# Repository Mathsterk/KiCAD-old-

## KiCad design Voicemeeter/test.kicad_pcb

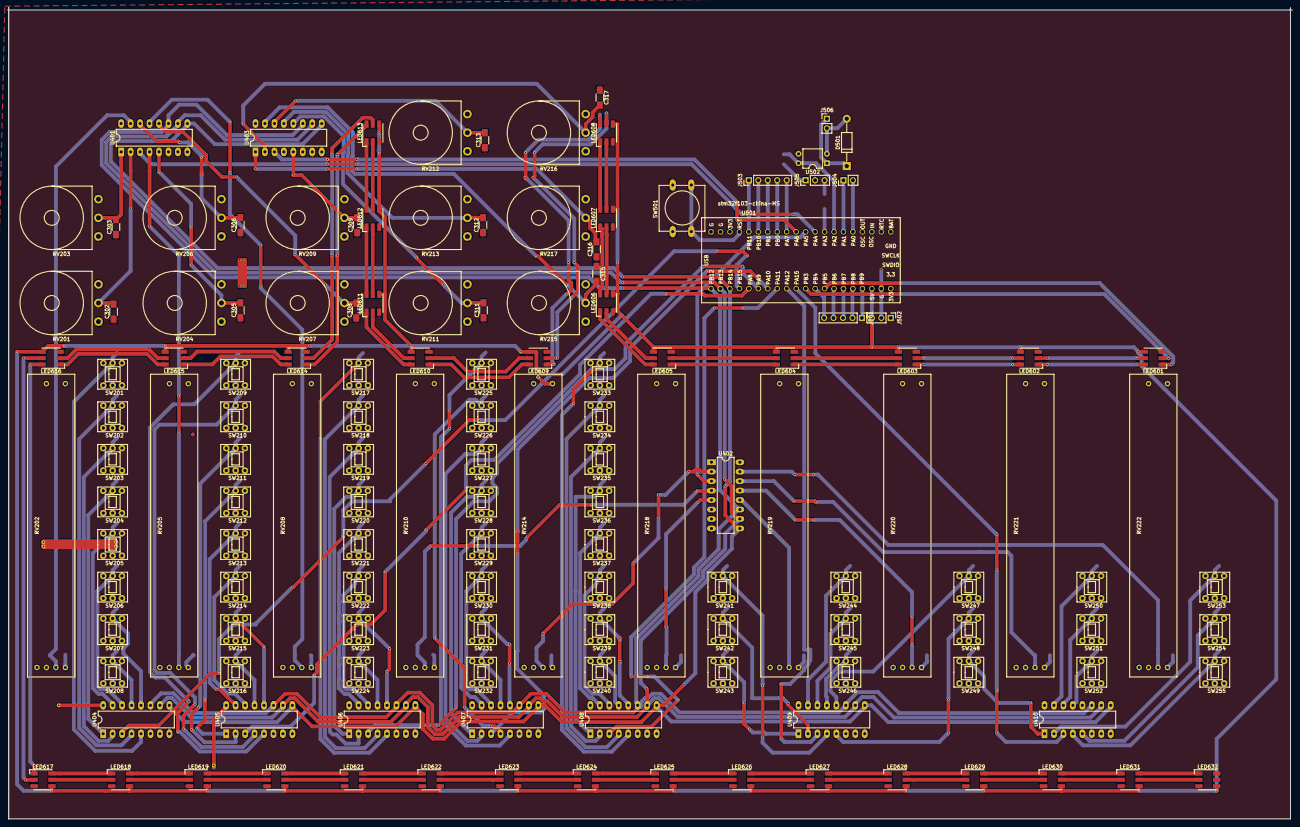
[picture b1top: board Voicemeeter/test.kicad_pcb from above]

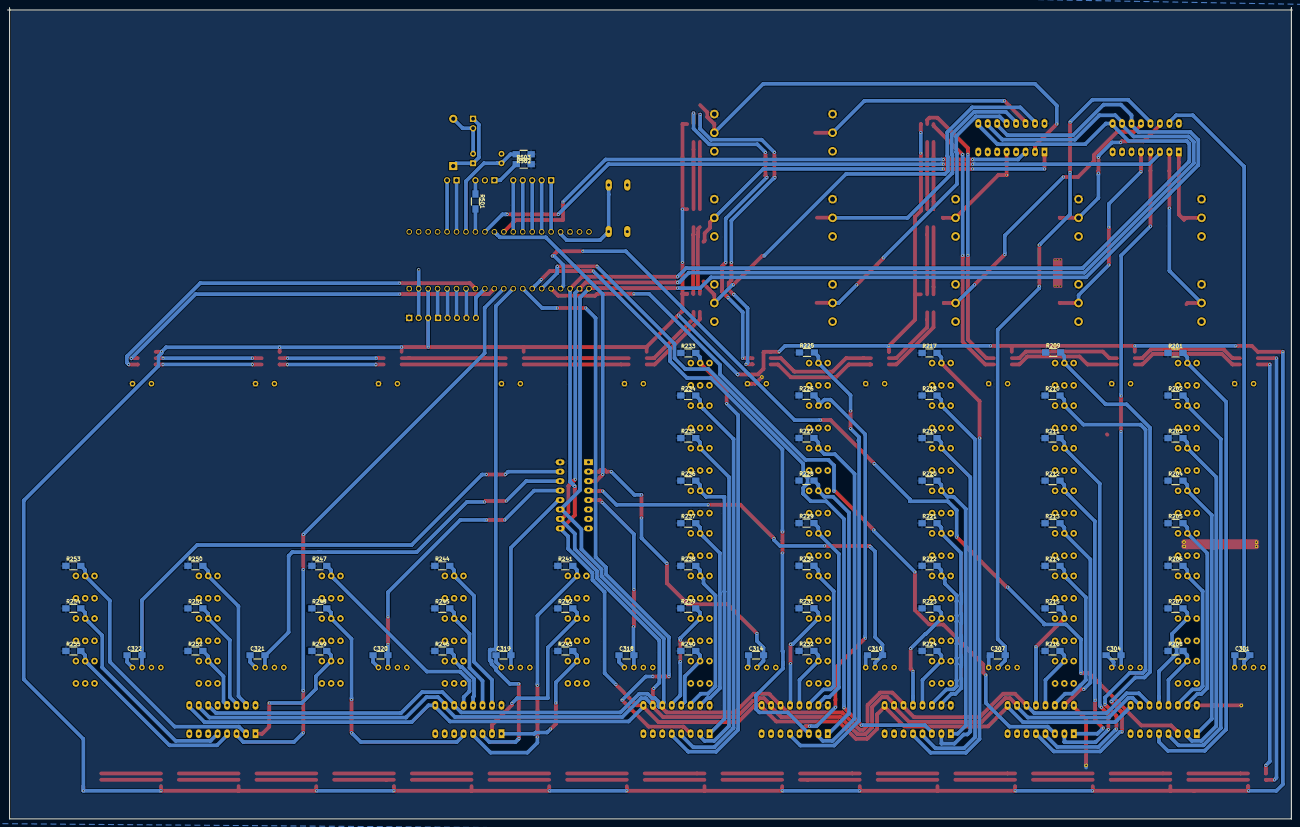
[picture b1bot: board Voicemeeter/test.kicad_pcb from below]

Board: 2 copper layers, 344.9 x 217.8 mm, 209 parts (68 on the bottom side), 176 nets.

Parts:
C301, C302, C303, C304, C305, C306, C307, C308, C309, C310, C311, C312, C313, C314, C315, C316, C317, C318, C319, C320, C321, C322: 10uF; C_1206_HandSoldering
D501: D; D_DO-41_SOD81_P12.70mm_Horizontal
J501, J503: CONN_01X05; Pin_Header_Straight_1x05_Pitch2.54mm
J502, J505: CONN_01X03; Pin_Header_Straight_1x03_Pitch2.54mm
J504, J506: CONN_01X02; Pin_Header_Straight_1x02_Pitch2.54mm
LED601, LED602, LED603, LED604, LED605, LED606, LED607, LED608, LED609, LED610, LED611, LED612, LED613, LED614, LED615, LED616, LED617, LED618, LED619, LED620, LED621, LED622, LED623, LED624, LED625, LED626, LED627, LED628, LED629, LED630, LED631, LED632: SK9822; LED_RGB_5050-6
R201, R202, R203, R204, R205, R206, R207, R208, R209, R210, R211, R212, R213, R214, R215, R216, R217, R218, R219, R220, R221, R222, R223, R224, R225, R226, R227, R228, R229, R230, R231, R232, R233, R234, R235, R236, R237, R238, R239, R240, R241, R242, R243, R244, R245, R246, R247, R248, R249, R250, R251, R252, R253, R254, R255: 10K; R_1206_HandSoldering
R501, R503: 220R; R_1206_HandSoldering
R502: 330R; R_1206_HandSoldering
RV201, RV203, RV204, RV206, RV207, RV209, RV211, RV212, RV213, RV215, RV216, RV217: POT; Potentiometer_Omeg_PC16PU_Horizontal
RV202, RV205, RV208, RV210, RV214, RV218, RV219, RV220, RV221, RV222: SLIDEPOT; slidepot
SW201, SW202, SW203, SW204, SW205, SW206, SW207, SW208, SW209, SW210, SW211, SW212, SW213, SW214, SW215, SW216, SW217, SW218, SW219, SW220, SW221, SW222, SW223, SW224, SW225, SW226, SW227, SW228, SW229, SW230, SW231, SW232, SW233, SW234, SW235, SW236, SW237, SW238, SW239, SW240, SW241, SW242, SW243, SW244, SW245, SW246, SW247, SW248, SW249, SW250, SW251, SW252, SW253, SW254, SW255: SW_SPDT_6pin; 8mm_push_button
SW501: SW_Push; SW_PUSH-12mm
U401, U402, U403, U404, U405, U406, U407, U408, U409, U410: 74HC4051; DIP-16_W7.62mm_LongPads
U501: stm32f103-china-MS; stm32f103c8t6-module-china-MS
U502: PC817; DIP-4_W7.62mm

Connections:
+3V3: J502.1, R201.1, R202.1, R203.1, R204.1, R205.1, R206.1, R207.1, R208.1, R209.1, R210.1, R211.1, R212.1, R213.1, R214.1, R215.1, R216.1, R217.1, R218.1, R219.1, R220.1, R221.1, R222.1, R223.1, R224.1, R225.1, R226.1, R227.1, R228.1, R229.1, R230.1, R231.1, R232.1, R233.1, R234.1, R235.1, R236.1, R237.1, R238.1, R239.1, R240.1, R241.1, R242.1, R243.1, R244.1, R245.1, R246.1, R247.1, R248.1, R249.1, R250.1, R251.1, R252.1, R253.1, R254.1, R255.1, R502.1, R503.2, RV201.1, RV202.3, RV203.1, RV204.1, RV205.3, RV206.1, RV207.1, RV208.3, RV209.1, RV210.3, RV211.1, RV212.1, RV213.1, RV214.3, RV215.1, RV216.1, RV217.1, RV218.3, RV219.3, RV220.3, RV221.3, RV222.3, U401.16, U402.16, U403.16, U404.16, U405.16, U406.16, U407.16, U408.16, U409.16, U410.16, U501.20, U501.38
+5V: J502.3, LED601.4, LED602.4, LED603.4, LED604.4, LED605.4, LED606.4, LED607.4, LED608.4, LED609.4, LED610.4, LED611.4, LED612.4, LED613.4, LED614.4, LED615.4, LED616.4, LED617.4, LED618.4, LED619.4, LED620.4, LED621.4, LED622.4, LED623.4, LED624.4, LED625.4, LED626.4, LED627.4, LED628.4, LED629.4, LED630.4, LED631.4, LED632.4, U501.18
/LED Driver/SK1: LED601.2, U501.11
/LED Driver/SK2: LED601.1, U501.13
/Mux/DA11: C310.2, RV210.2, U402.4
/Mux/DA12: C311.2, RV211.2, U403.12
/Mux/DA13: C312.2, RV213.2, U403.13
/Mux/DA14: C313.2, RV212.2, U403.14
/Mux/DA21: C314.2, RV214.2, U402.2
/Mux/DA22: C315.2, RV215.2, U403.15
/Mux/DA23: C316.2, RV217.2, U403.1
/Mux/DA24: C317.2, RV216.2, U403.2
/Mux/DD11: R225.2, SW225.1, U407.5
/Mux/DD12: R226.2, SW226.1, U407.4
/Mux/DD13: R227.2, SW227.1, U407.2
/Mux/DD14: R228.2, SW228.1, U407.1
/Mux/DD15: R229.2, SW229.1, U407.15
/Mux/DD16: R230.2, SW230.1, U407.14
/Mux/DD17: R231.2, SW231.1, U407.12
/Mux/DD18: R232.2, SW232.1, U407.13
/Mux/DD21: R233.2, SW233.1, U408.5
/Mux/DD22: R234.2, SW234.1, U408.4
/Mux/DD23: R235.2, SW235.1, U408.2
/Mux/DD24: R236.2, SW236.1, U408.1
/Mux/DD25: R237.2, SW237.1, U408.15
/Mux/DD26: R238.2, SW238.1, U408.14
/Mux/DD27: R239.2, SW239.1, U408.12
/Mux/DD28: R240.2, SW240.1, U408.13
/Mux/HA11: C301.2, RV202.2, U401.15
/Mux/HA12: C302.2, RV201.2, U401.2
/Mux/HA13: C303.2, RV203.2, U401.1
/Mux/HA21: C304.2, RV205.2, U401.4
/Mux/HA22: C305.2, RV204.2, U401.5
/Mux/HA23: C306.2, RV206.2, U401.14
/Mux/HA31: C307.2, RV208.2, U401.13
/Mux/HA32: C308.2, RV207.2, U401.12
/Mux/HA33: C309.2, RV209.2, U403.5
/Mux/HD11: R201.2, SW201.1, U404.5
/Mux/HD12: R202.2, SW202.1, U404.4
/Mux/HD13: R203.2, SW203.1, U404.2
/Mux/HD14: R204.2, SW204.1, U404.1
/Mux/HD15: R205.2, SW205.1, U404.15
/Mux/HD16: R206.2, SW206.1, U404.14
/Mux/HD17: R207.2, SW207.1, U404.12
/Mux/HD18: R208.2, SW208.1, U404.13
/Mux/HD21: R209.2, SW209.1, U405.5
/Mux/HD22: R210.2, SW210.1, U405.4
/Mux/HD23: R211.2, SW211.1, U405.2
/Mux/HD24: R212.2, SW212.1, U405.1
/Mux/HD25: R213.2, SW213.1, U405.15
/Mux/HD26: R214.2, SW214.1, U405.14
/Mux/HD27: R215.2, SW215.1, U405.12
/Mux/HD28: R216.2, SW216.1, U405.13
/Mux/HD31: R217.2, SW217.1, U406.5
/Mux/HD32: R218.2, SW218.1, U406.4
/Mux/HD33: R219.2, SW219.1, U406.2
/Mux/HD34: R220.2, SW220.1, U406.1
/Mux/HD35: R221.2, SW221.1, U406.15
/Mux/HD36: R222.2, SW222.1, U406.14
/Mux/HD37: R223.2, SW223.1, U406.12
/Mux/HD38: R224.2, SW224.1, U406.13
/Mux/M1: U401.11, U402.11, U403.11, U404.11, U405.11, U406.11, U407.11, U408.11, U409.11, U410.11, U501.1
/Mux/M2: U401.10, U402.10, U403.10, U404.10, U405.10, U406.10, U407.10, U408.10, U409.10, U410.10, U501.2
/Mux/M3: U401.9, U402.9, U403.9, U404.9, U405.9, U406.9, U407.9, U408.9, U409.9, U410.9, U501.3
/Mux/M11: U401.3, U501.29
/Mux/M12: U402.3, U501.30
/Mux/M13: U403.3, U501.31
/Mux/M21: U404.3, U501.4
/Mux/M22: U405.3, U501.5
/Mux/M23: U406.3, U501.6
/Mux/M24: U407.3, U501.7
/Mux/M25: U408.3, U501.8
/Mux/M26: U409.3, U501.9
/Mux/M27: U410.3, U501.10
/Mux/OA1: C318.2, RV218.2, U402.5
/Mux/OA2: C319.2, RV219.2, U402.12
/Mux/OA3: C320.2, RV220.2, U402.13
/Mux/OA4: C321.2, RV221.2, U402.14
/Mux/OA5: C322.2, RV222.2, U402.15
/Mux/OD11: R241.2, SW241.1, U409.4
/Mux/OD12: R242.2, SW242.1, U409.2
/Mux/OD13: R243.2, SW243.1, U409.1
/Mux/OD21: R244.2, SW244.1, U409.15
/Mux/OD22: R245.2, SW245.1, U409.14
/Mux/OD23: R246.2, SW246.1, U409.13
/Mux/OD31: R247.2, SW247.1, U409.12
/Mux/OD32: R248.2, SW248.1, U409.5
/Mux/OD33: R249.2, SW249.1, U410.1
/Mux/OD41: R250.2, SW250.1, U410.15
/Mux/OD42: R251.2, SW251.1, U410.14
/Mux/OD43: R252.2, SW252.1, U410.13
/Mux/OD51: R253.2, SW253.1, U410.2
/Mux/OD52: R254.2, SW254.1, U410.5
/Mux/OD53: R255.2, SW255.1, U410.4
GND: C301.1, C302.1, C303.1, C304.1, C305.1, C306.1, C307.1, C308.1, C309.1, C310.1, C311.1, C312.1, C313.1, C314.1, C315.1, C316.1, C317.1, C318.1, C319.1, C320.1, C321.1, C322.1, J502.2, J505.2, LED601.3, LED602.3, LED603.3, LED604.3, LED605.3, LED606.3, LED607.3, LED608.3, LED609.3, LED610.3, LED611.3, LED612.3, LED613.3, LED614.3, LED615.3, LED616.3, LED617.3, LED618.3, LED619.3, LED620.3, LED621.3, LED622.3, LED623.3, LED624.3, LED625.3, LED626.3, LED627.3, LED628.3, LED629.3, LED630.3, LED631.3, LED632.3, RV201.3, RV202.1, RV203.3, RV204.3, RV205.1, RV206.3, RV207.3, RV208.1, RV209.3, RV210.1, RV211.3, RV212.3, RV213.3, RV214.1, RV215.3, RV216.3, RV217.3, RV218.1, RV219.1, RV220.1, RV221.1, RV222.1, SW201.2, SW201.4, SW201.5, SW201.6, SW202.2, SW202.4, SW202.5, SW202.6, SW203.2, SW203.4, SW203.5, SW203.6, SW204.2, SW204.4, SW204.5, SW204.6, SW205.2, SW205.4, SW205.5, SW205.6, SW206.2, SW206.4, SW206.5, SW206.6, SW207.2, SW207.4, SW207.5, SW207.6, SW208.2, SW208.4, SW208.5, SW208.6, SW209.2, SW209.4, SW209.5, SW209.6, SW210.2, SW210.4, SW210.5, SW210.6, SW211.2, SW211.4, SW211.5, SW211.6, SW212.2, SW212.4, SW212.5, SW212.6, SW213.2, SW213.4, SW213.5, SW213.6, SW214.2, SW214.4, SW214.5, SW214.6, SW215.2, SW215.4, SW215.5, SW215.6, SW216.2, SW216.4, SW216.5, SW216.6, SW217.2, SW217.4, SW217.5, SW217.6, SW218.2, SW218.4, SW218.5, SW218.6, SW219.2, SW219.4, SW219.5, SW219.6, SW220.2, SW220.4, SW220.5, SW220.6, SW221.2, SW221.4, SW221.5, SW221.6, SW222.2, SW222.4, SW222.5, SW222.6, SW223.2, SW223.4, SW223.5, SW223.6, SW224.2, SW224.4, SW224.5, SW224.6, SW225.2, SW225.4, SW225.5, SW225.6, SW226.2, SW226.4, SW226.5, SW226.6, SW227.2, SW227.4, SW227.5, SW227.6, SW228.2, SW228.4, SW228.5, SW228.6, SW229.2, SW229.4, SW229.5, SW229.6, SW230.2, SW230.4, SW230.5, SW230.6, SW231.2, SW231.4, SW231.5, SW231.6, SW232.2, SW232.4, SW232.5, SW232.6, SW233.2, SW233.4, SW233.5, SW233.6, SW234.2, SW234.4, SW234.5, SW234.6, SW235.2, SW235.4, SW235.5, SW235.6, SW236.2, SW236.4, SW236.5, SW236.6, SW237.2, SW237.4, SW237.5, SW237.6, SW238.2, SW238.4, SW238.5, SW238.6, SW239.2, SW239.4, SW239.5, SW239.6, SW240.2, SW240.4, SW240.5, SW240.6, SW241.2, SW241.4, SW241.5, SW241.6, SW242.2, SW242.4, SW242.5, SW242.6, SW243.2, SW243.4, SW243.5, SW243.6, SW244.2, SW244.4, SW244.5, SW244.6, SW245.2, SW245.4, SW245.5, SW245.6, SW246.2, SW246.4, SW246.5, SW246.6, SW247.2, SW247.4, SW247.5, SW247.6, SW248.2, SW248.4, SW248.5, SW248.6, SW249.2, SW249.4, SW249.5, SW249.6, SW250.2, SW250.4, SW250.5, SW250.6, SW251.2, SW251.4, SW251.5, SW251.6, SW252.2, SW252.4, SW252.5, SW252.6, SW253.2, SW253.4, SW253.5, SW253.6, SW254.2, SW254.4, SW254.5, SW254.6, SW255.2, SW255.4, SW255.5, SW255.6, SW501.1, U401.8, U402.8, U403.8, U404.8, U405.8, U406.8, U407.8, U408.8, U409.8, U410.8, U501.19, U501.39, U501.40, U502.3
unnamed: D501.1, J506.1, U502.1
unnamed: D501.2, J506.2, U502.2
unnamed: J501.1, U501.17
unnamed: J501.2, U501.16
unnamed: J501.3, U501.15
unnamed: J501.4, U501.14
unnamed: J501.5, U501.12
unnamed: J503.1, U501.36
unnamed: J503.2, U501.35
unnamed: J503.3, U501.34
unnamed: J503.4, U501.33
unnamed: J503.5, U501.32
unnamed: J504.1, U501.26
unnamed: J504.2, U501.25
unnamed: J505.1, R503.1
unnamed: J505.3, R501.1
unnamed: LED601.5, LED602.2
unnamed: LED601.6, LED602.1
unnamed: LED602.5, LED603.2
unnamed: LED602.6, LED603.1
unnamed: LED603.5, LED604.2
unnamed: LED603.6, LED604.1
unnamed: LED604.5, LED605.2
unnamed: LED604.6, LED605.1
unnamed: LED605.5, LED606.2
unnamed: LED605.6, LED606.1
unnamed: LED606.5, LED607.2
unnamed: LED606.6, LED607.1
unnamed: LED607.5, LED608.2
unnamed: LED607.6, LED608.1
unnamed: LED608.5, LED609.2
unnamed: LED608.6, LED609.1
unnamed: LED609.5, LED610.2
unnamed: LED609.6, LED610.1
unnamed: LED610.5, LED611.2
unnamed: LED610.6, LED611.1
unnamed: LED611.5, LED612.2
unnamed: LED611.6, LED612.1
unnamed: LED612.5, LED613.2
unnamed: LED612.6, LED613.1
unnamed: LED613.5, LED614.2
unnamed: LED613.6, LED614.1
unnamed: LED614.5, LED615.2
unnamed: LED614.6, LED615.1
unnamed: LED615.5, LED616.2
unnamed: LED615.6, LED616.1
unnamed: LED616.5, LED617.2
unnamed: LED616.6, LED617.1
unnamed: LED617.5, LED618.2
unnamed: LED617.6, LED618.1
unnamed: LED618.5, LED619.2
unnamed: LED618.6, LED619.1
unnamed: LED619.5, LED620.2
unnamed: LED619.6, LED620.1
unnamed: LED620.5, LED621.2
unnamed: LED620.6, LED621.1
unnamed: LED621.5, LED622.2
unnamed: LED621.6, LED622.1
unnamed: LED622.5, LED623.2
unnamed: LED622.6, LED623.1
unnamed: LED623.5, LED624.2
unnamed: LED623.6, LED624.1
unnamed: LED624.5, LED625.2
unnamed: LED624.6, LED625.1
unnamed: LED625.5, LED626.2
unnamed: LED625.6, LED626.1
unnamed: LED626.5, LED627.2
unnamed: LED626.6, LED627.1
unnamed: LED627.5, LED628.2
unnamed: LED627.6, LED628.1
unnamed: LED628.5, LED629.2
unnamed: LED628.6, LED629.1
unnamed: LED629.5, LED630.2
unnamed: LED629.6, LED630.1
unnamed: LED630.5, LED631.2
unnamed: LED630.6, LED631.1
unnamed: LED631.5, LED632.2
unnamed: LED631.6, LED632.1
unnamed: R501.2, U501.28
unnamed: R502.2, U501.27, U502.4
unnamed: SW501.2, U501.37

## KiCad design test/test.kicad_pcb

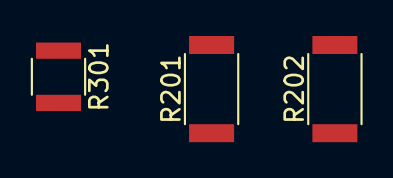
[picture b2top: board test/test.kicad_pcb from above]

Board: 2 copper layers, 3 parts (0 on the bottom side), 2 nets, no tracks yet.

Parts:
R201, R202: R; R_2010
R301: R; R_1210

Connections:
/Sheet5AE77FCA/a1: R201.2, R202.2, R301.1
/Sheet5AE77FCA/a2: R201.1, R202.1, R301.2

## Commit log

2018-03-07 FM first
2018-03-07 asdasdasd
2018-05-08 rrr
    asd
